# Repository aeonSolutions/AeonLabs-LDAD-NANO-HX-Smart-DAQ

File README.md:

[PCB-Prototyping-Catalogue](https://github.com/aeonSolutions/PCB-Prototyping-Catalogue)  >>  [Laboratory Automation](https://github.com/aeonSolutions/PCB-Prototyping-Catalogue/tree/main/Laboratory%20Automation) >>  [Smart DAQ](https://github.com/aeonSolutions/PCB-Prototyping-Catalogue/tree/main/Smart%20DAQ)  >>   [12-bit Smart DAQs](https://github.com/aeonSolutions/PCB-Prototyping-Catalogue/tree/main/Smart%20DAQ/12-bit)  >>  LDAD NANO HX Smart DAQ

<br>

#  LDAD NANO HX Smart DAQ
This repo contains the KiCad files for the  AeonLabs  LDAD NANO for strain sensing / weight measurements and more than 20 other sensors compatible with I2C protocol communication. 
 
*Don't forget to LIKE , SHARE and subscribe the free whatsApp group* and if you liked this PCB consider buying me a cup of coffee. Links below.

###   Status

Fully working.

## Download options
Download this repository if you need the KiCad Files or, download the Gerber files in the release section of this repository

## Liked it ? Get a Free PCB for yourself
Send me your Device or hardware and i will design a custom PCB for it. Free of charge. Contact-me on WhatsApp or email for more info. 

## Q&A WhatsApp Group
If you have any Questions or simply  like this kind of projects and want to stay updated with the latest research ideas and prototypes during the day and week, join the WhatsApp Group
[LDAD Lab & Prototyping](https://chat.whatsapp.com/FkNC7u83kuy2QRA5sqjBVg)

## Fully assembled PCB
Alternatively, and if you do not want to build a PCB by yourself and like to buy one, you can do it here:

The price will be around 30eur plus postage fees.
(I will also deliver the assembled PCB with all the components in place at a fair aditonal cost).

#### Be supportive of my dedication and work towards technology education and buy me a coffee. Link below.

________________________________________________________________________________________________________________
## [Go back to main catalogue page](https://github.com/aeonSolutions/PCB-Prototyping-Catalogue)
________________________________________________________________________________________________________________

## PCB Parts list
- DC2DC converter HX4002B x2 : https://s.click.aliexpress.com/e/_Ak7IPx
- Capacitor 100nF SMD 1206 : https://s.click.aliexpress.com/e/_AVdmzr
- Capacitor 2.2uF SMD 1206 : https://s.click.aliexpress.com/e/_AVdmzr
- Resistor SMD 1206 330R x3 : https://s.click.aliexpress.com/e/_A7OXrR
- ESP32 WROOM32 x1 : https://s.click.aliexpress.com/e/_AF7N6l
- LED RGB x1: https://s.click.aliexpress.com/e/_AccXHT

## Firmware Download 
one can use the PCB in the repository [AeonLabs-MCU-Burner-USB-to-UART-TTL](https://github.com/aeonSolutions/AeonLabs-MCU-Burner-USB-to-UART-TTL) to program the ESP32 WROOM32 MCU on this PCB.

______________________________________________________________________________________________________________________________

### License
2022 Creative Commons Attribution-NonCommercial-ShareAlike 4.0 International

https://creativecommons.org/licenses/by-nc-sa/4.0/

### Own a copy of this work
if you like to own a copy of this work, you can buy it as a NFT or Ethereum. contact me for more details at mtpsilva@gmail.com

=====================================================================================
### Share this PCB board files

### Be supportive of my dedication and work towards technology education and buy me a coffee

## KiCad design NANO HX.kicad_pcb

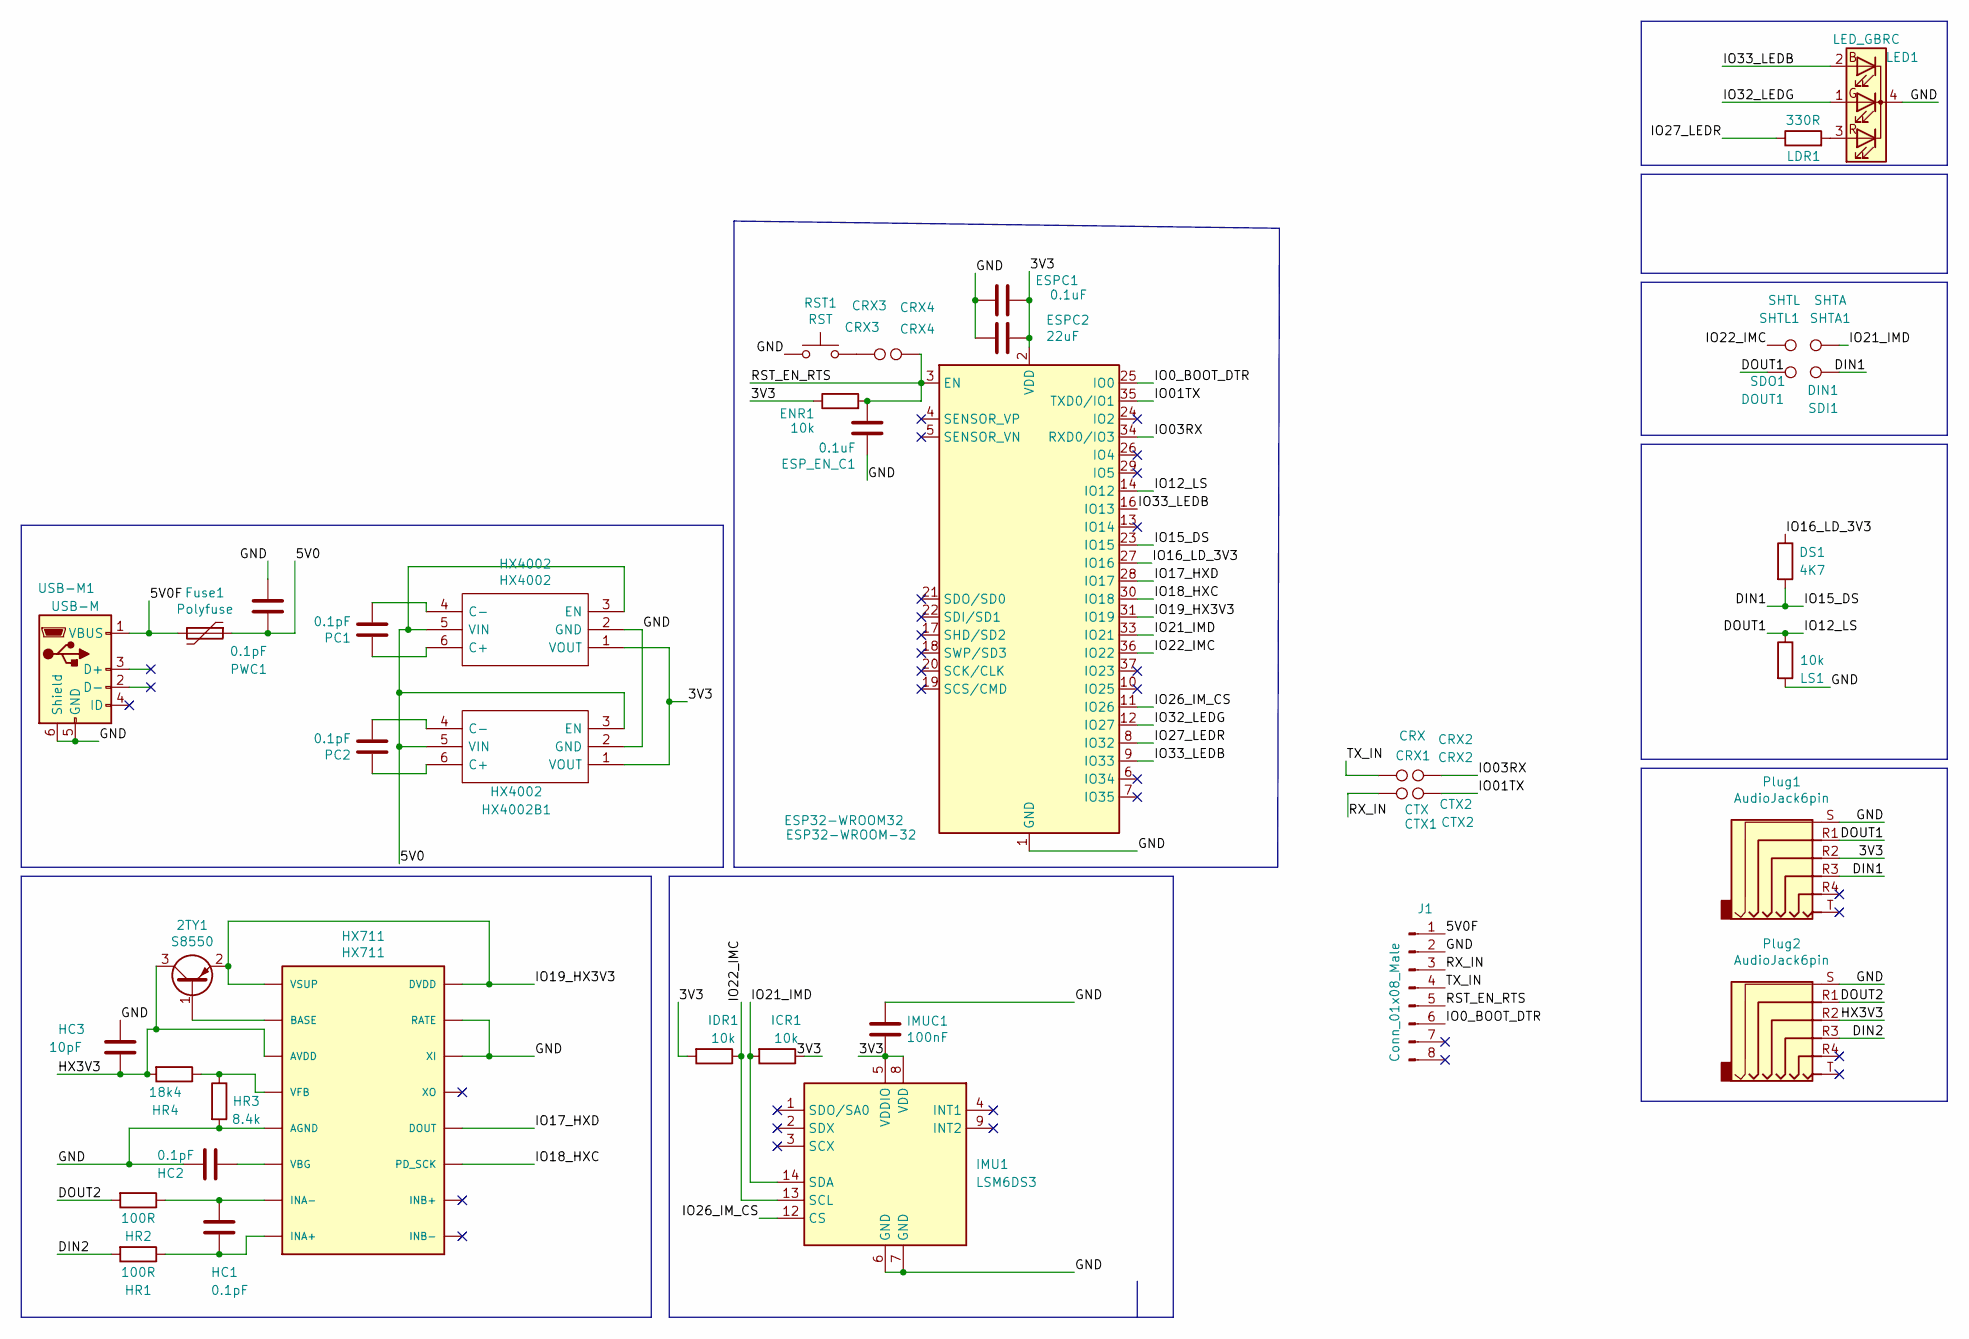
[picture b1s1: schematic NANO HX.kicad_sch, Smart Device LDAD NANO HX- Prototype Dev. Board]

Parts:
2TY1: S8550; SOT-23
CRX1: CRX; TestPoint_Pad_1.0x1.0mm
CRX2: CRX2; TestPoint_Pad_1.0x1.0mm
CRX3: CRX3; TestPoint_Pad_1.0x1.0mm
CRX4: CRX4; TestPoint_Pad_1.0x1.0mm
CTX1: CTX; TestPoint_Pad_1.0x1.0mm
CTX2: CTX2; TestPoint_Pad_1.0x1.0mm
DS1: 4K7; R_0805_2012Metric_Pad1.20x1.40mm_HandSolder
ENR1: 10k; R_0805_2012Metric_Pad1.20x1.40mm_HandSolder
ESP32-WROOM32: ESP32-WROOM-32
ESPC1: 0.1uF; C_0805_2012Metric_Pad1.18x1.45mm_HandSolder
ESPC2: 22uF; C_0805_2012Metric_Pad1.18x1.45mm_HandSolder
ESP_EN_C1: 0.1uF; C_0805_2012Metric_Pad1.18x1.45mm_HandSolder
Fuse1: Polyfuse; Fuse_1206_3216Metric
HC1, HC2: 0.1pF; C_0805_2012Metric_Pad1.18x1.45mm_HandSolder
HC3: 10pF; C_0805_2012Metric_Pad1.18x1.45mm_HandSolder
HR1, HR2: 100R; R_0805_2012Metric_Pad1.20x1.40mm_HandSolder
HR3: 8.4k; R_0805_2012Metric_Pad1.20x1.40mm_HandSolder
HR4: 18k4; R_0805_2012Metric_Pad1.20x1.40mm_HandSolder
HX711: HX711; SO16
HX4002, HX4002B1: HX4002; HX4002 SOT95 P280X125-6N; Manufacturer_Part_Number HX4002
ICR1: 10k; R_0805_2012Metric_Pad1.20x1.40mm_HandSolder
IDR1: 10k; R_0805_2012Metric_Pad1.20x1.40mm_HandSolder
IMU1: LSM6DS3; LGA-14_3x2.5mm_P0.5mm_LayoutBorder3x4y
IMUC1: 100nF; C_0805_2012Metric_Pad1.18x1.45mm_HandSolder
J1: Conn_01x08_Male; SOIC_clipProgSmall
LDR1: 330R; R_0805_2012Metric_Pad1.20x1.40mm_HandSolder
LED1: LED_GBRC; LED_1206_3210_RGB_Metric
LS1: 10k; R_0805_2012Metric_Pad1.20x1.40mm_HandSolder
PC1, PC2: 0.1pF; C_0805_2012Metric_Pad1.18x1.45mm_HandSolder
PWC1: 0.1pF; C_0805_2012Metric_Pad1.18x1.45mm_HandSolder
Plug1, Plug2: AudioJack6pin; Jack 2.5mm jack socket 6pin L10.5 w5.8 h3.2
RST1: RST; SW_Push_SPST_NO_Alps_SKRK AliExpress
SDI1: DIN1; TestPoint_Pad_1.0x1.0mm
SDO1: DOUT1; TestPoint_Pad_1.0x1.0mm
SHTA1: SHTA; TestPoint_Pad_1.0x1.0mm
SHTL1: SHTL; TestPoint_Pad_1.0x1.0mm
USB-M1: USB-M; Micro_USB_pcb_socket_5pin_4weld_points

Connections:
/3V3: ENR1.1, ESP32-WROOM32.2 (VDD), ESPC1.1, ESPC2.1, HX4002.1 (VOUT), HX4002B1.1 (VOUT), ICR1.1, IDR1.2, IMU1.5 (VDDIO), IMU1.8 (VDD), IMUC1.2, Plug1.R2
/5V0: Fuse1.1, HX4002.3 (EN), HX4002.5 (VIN), HX4002B1.3 (EN), HX4002B1.5 (VIN), PWC1.1
/5V0F: Fuse1.2, J1.1, USB-M1.1 (VBUS)
/DIN1: DS1.2, ESP32-WROOM32.23 (IO15), Plug1.R3, SDI1.1
/DIN2: HR1.2, Plug2.R3
/DOUT1: ESP32-WROOM32.14 (IO12), LS1.1, Plug1.R1, SDO1.1
/DOUT2: HR2.2, Plug2.R1
/GND: ESP32-WROOM32.1 (GND), ESP32-WROOM32.15 (GND), ESP32-WROOM32.38 (GND), ESP32-WROOM32.39 (GND), ESPC1.2, ESPC2.2, ESP_EN_C1.1, HC2.2, HC3.1, HR3.2, HX711.5 (AGND), HX711.14 (XI), HX711.15 (RATE), HX4002.2 (GND), HX4002B1.2 (GND), IMU1.6 (GND), IMU1.7 (GND), IMUC1.1, J1.2, LED1.4 (K), LS1.2, PWC1.2, Plug1.S, Plug2.S, RST1.1, USB-M1.5 (GND), USB-M1.6 (Shield)
/HX3V3: 2TY1.3 (C), HC3.2, HR4.2, HX711.3 (AVDD), Plug2.R2
/IO0_BOOT_DTR: ESP32-WROOM32.25 (IO0), J1.6
/IO01TX: CTX2.1, ESP32-WROOM32.35 (TXD0/IO1)
/IO03RX: CRX2.1, ESP32-WROOM32.34 (RXD0/IO3)
/IO16_LD_3V3: DS1.1, ESP32-WROOM32.27 (IO16)
/IO17_HXD: ESP32-WROOM32.28 (IO17), HX711.12 (DOUT)
/IO18_HXC: ESP32-WROOM32.30 (IO18), HX711.11 (PD_SCK)
/IO19_HX3V3: 2TY1.2 (E), ESP32-WROOM32.31 (IO19), HX711.1 (VSUP), HX711.16 (DVDD)
/IO21_IMD: ESP32-WROOM32.33 (IO21), ICR1.2, IMU1.14 (SDA), SHTA1.1
/IO22_IMC: ESP32-WROOM32.36 (IO22), IDR1.1, IMU1.13 (SCL), SHTL1.1
/IO26_IM_CS: ESP32-WROOM32.11 (IO26), IMU1.12 (CS)
/IO27_LEDR: ESP32-WROOM32.8 (IO32), LDR1.1
/IO32_LEDG: ESP32-WROOM32.12 (IO27), LED1.1 (GA)
/IO33_LEDB: ESP32-WROOM32.9 (IO33), ESP32-WROOM32.16 (IO13), LED1.2 (BA)
/RST_EN_RTS: CRX4.1, ENR1.2, ESP32-WROOM32.3 (EN), ESP_EN_C1.2, J1.5
/RX_IN: CTX1.1, J1.3
/TX_IN: CRX1.1, J1.4
unnamed: 2TY1.1 (B), HX711.2 (BASE)
unnamed: CRX3.1, RST1.2
unnamed: HC1.1, HR2.1, HX711.7 (INA-)
unnamed: HC1.2, HR1.1, HX711.8 (INA+)
unnamed: HC2.1, HX711.6 (VBG)
unnamed: HR3.1, HR4.1, HX711.4 (VFB)
unnamed: HX4002.4 (C-), PC1.2
unnamed: HX4002.6 (C+), PC1.1
unnamed: HX4002B1.4 (C-), PC2.2
unnamed: HX4002B1.6 (C+), PC2.1
unnamed: LDR1.2, LED1.3 (RA)

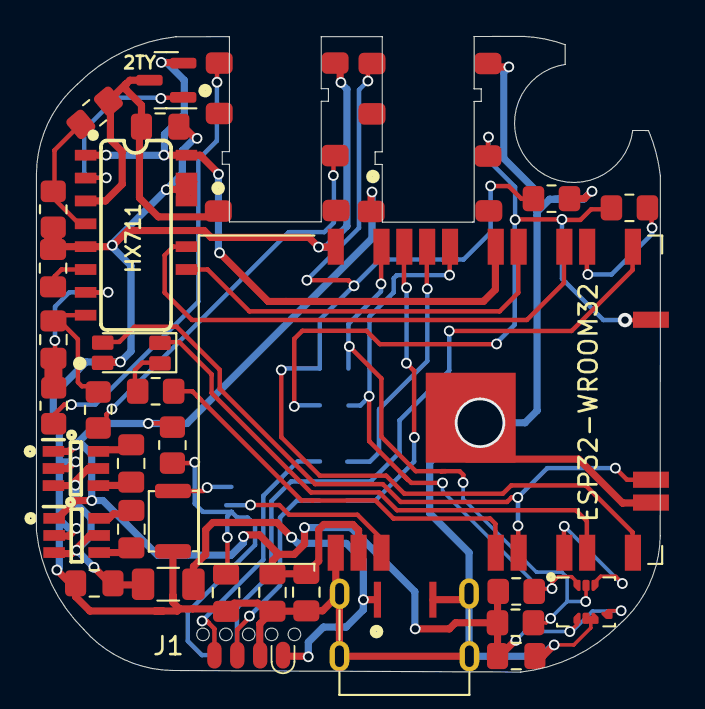
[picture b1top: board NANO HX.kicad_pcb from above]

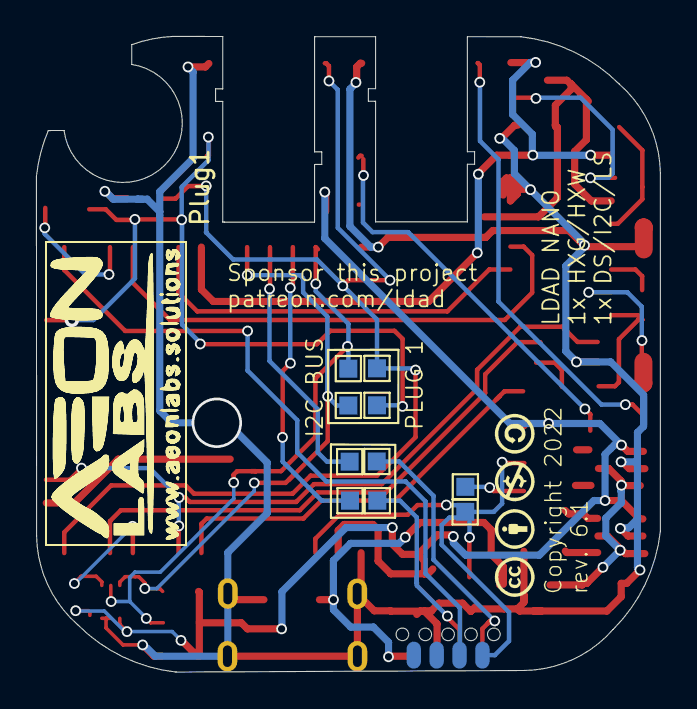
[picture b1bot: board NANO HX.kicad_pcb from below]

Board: 2 copper layers, 34.7 x 35.3 mm, 43 parts (10 on the bottom side), 36 nets.

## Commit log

2022-04-02 init comm

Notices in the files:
NANO HX.kicad_pcb:
Copyright 2022
